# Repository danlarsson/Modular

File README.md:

# My Modular
My Modular Eurorack Synth

The plan is to build every module myself, with help from the all mighty internet to get schematics and tips.

KiCad 7.0 is used to create the schematics and PCBs.
PCBWay or JLCPCB is used for the PCBs.

# Planned Modules:

## 1. PSU: Power supply + Breakout board + Frontpanel
  - Power Supply 
    - [X] Design, [X] Order, [] Build, [] Test
 
  - Breakout board
    - [] Design, [] Order, [] Build, [] Test

  - Front panel
    - [] Design, [] Order, [] Build, [] Test

## 2. VCO: Voltage Conntrolled Oscillator
 ### VCO_1
  - [] Design, [] Order, [] Build, [] Test

## 3. VCF: Filter:

## 4. Envelope Generator:

## 5. LFO: Low Freq Oscillator

## 6. VCA: Voltage Controlled Amplifier

## 7. Mixer:

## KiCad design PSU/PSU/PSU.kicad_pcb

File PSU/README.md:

# PSU
A PowerSuply that converts 12-15V AC to +12, -12 and 5 Volts.
Containt 3 parts the PSU a Power Rail and a Front panel with a switch and LEDs.

# PDB
Power Distribution Board

# Front Panel
Front Panel for the PSU, with LED indicators and a Connector to get power for experiments.

## Idéas from:
https://www.patreon.com/moritzklein/posts?filters%5Btag%5D=PSU%20series

http://musicfromouterspace.com/analogsynth_new/WALLWARTSUPPLY/wallwart_added_load_rs_schem.pdf

## Parts:
6st - 4700uF 35V Elec Cap
https://www.lcsc.com/product-detail/Aluminum-Electrolytic-Capacitors-Leaded_CX-Dongguan-Chengxing-Elec-KM478M035L30RR0VH2FP0_C43354.html

6st 1uF 35V Tantalum Cap
https://www.lcsc.com/product-detail/span-style-background-color-ff0-Tantalum-span-Capacitors_Kyocera-AVX-TAP105K035SCS_C2987014.html

4st 1N4007  DO-41
https://www.lcsc.com/product-detail/Diodes-General-Purpose_ST-Semtech-1N4007_C106903.html

1st LC7812  TO-220
https://www.lcsc.com/product-detail/Linear-Voltage-Regulators-LDO_STMicroelectronics-L7812CV-DG_C2914.html

1st LC7912
https://www.lcsc.com/product-detail/Linear-Voltage-Regulators-LDO_STMicroelectronics-L7912CV_C111886.html

1st LC7805
https://www.lcsc.com/product-detail/Linear-Voltage-Regulators-LDO_STMicroelectronics-L7805CV_C111887.html

3st Heat Sink TO-220
https://www.lcsc.com/products/Heat-Sinks_441.html
https://www.lcsc.com/product-detail/Heat-Sinks_XSD-C4649_C4649.html

3st TO-220 Isolator
https://www.lcsc.com/product-detail/Heat-Sinks_Made-in-China-TO-220_C3010573.html

Skruv + Mutter + Isolator
https://www.lcsc.com/product-detail/Heat-Sinks_Made-in-China-C13380_C13380.html 

1st 16pin IDC Connector
https://www.lcsc.com/product-detail/span-style-background-color-ff0-IDC-span-span-style-background-color-ff0-Connectors-span_BOOMELE-Boom-Precision-Elec-C3406_C3406.html

1st 4pin screw terminal
https://www.lcsc.com/product-detail/span-style-background-color-ff0-Screw-span-span-style-background-color-ff0-terminal-span_DIBO-DB128L-5-0-4P-BU-S_C430599.html

1st 2pin screw terminal
https://www.lcsc.com/product-detail/Screw-terminal_DIBO-DB103-5-0-2P-BU-S_C430581.html

1st 2pin connector
?

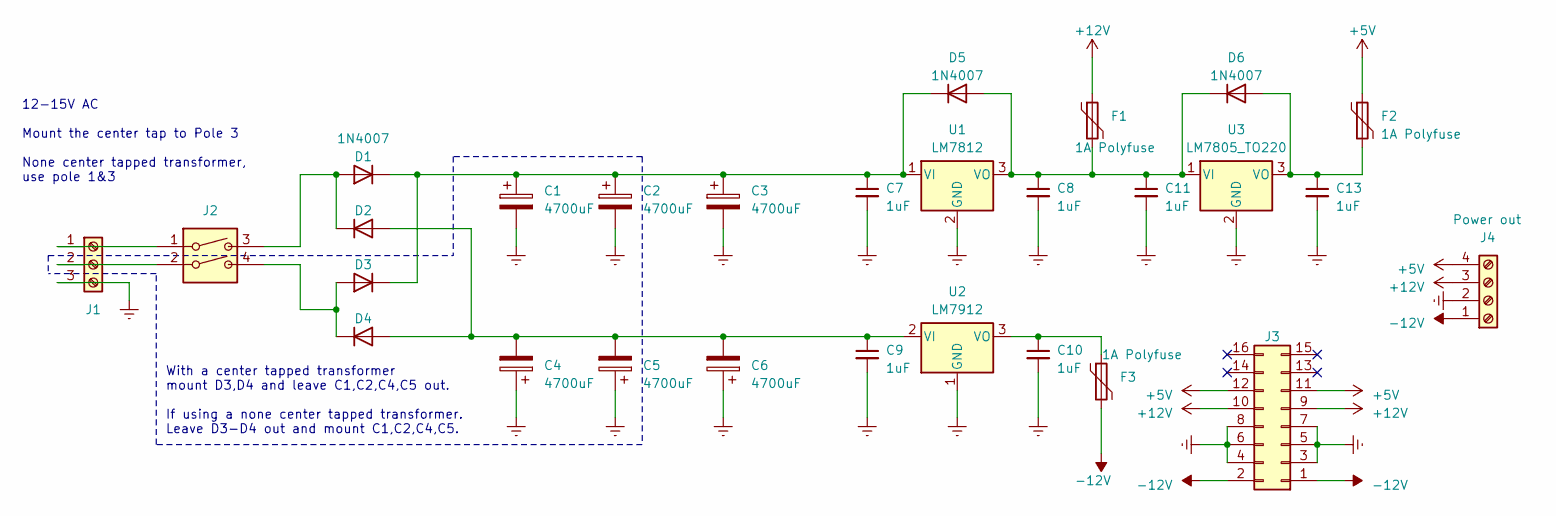
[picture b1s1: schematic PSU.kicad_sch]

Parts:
C1, C2, C3, C4, C5, C6: 4700uF; CP_Radial_D18.0mm_P7.50mm
C7, C8, C9, C10, C11, C13: 1uF; C_Rect_L7.0mm_W3.5mm_P5.00mm
D1, D2, D3, D4, D5, D6: 1N4007; D_DO-41_SOD81_P10.16mm_Horizontal
F1, F2, F3: 1A Polyfuse; Fuse_Bourns_MF-RHT200
J1: Screw_Terminal_01x03; JST_NV_B03P-NV_1x03_P5.00mm_Vertical
J2: SW_DIP_x02; PinSocket_2x02_P2.54mm_Vertical
J3: Conn_02x08_Odd_Even; IDC-Header_2x08_P2.54mm_Vertical
J4: Power out; JST_NV_B04P-NV_1x04_P5.00mm_Vertical
U1: LM7812; TO-220-3_Vertical
U2: LM7912; TO-220-3_Vertical
U3: LM7805_TO220; TO-220-3_Vertical

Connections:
+5V: F2.1, J3.11, J3.12, J4.4
+12V: F1.1, J3.9, J3.10, J4.3
-12V: F3.2, J3.1, J3.2, J4.1
GNDREF: C1.2, C2.2, C3.2, C4.1, C5.1, C6.1, C7.2, C8.2, C9.2, C10.2, C11.2, C13.2, J1.3, J3.3, J3.4, J3.5, J3.6, J3.7, J3.8, J4.2, U1.2 (GND), U2.1 (GND), U3.2 (GND)
unnamed: D1.2 (A), D2.1 (K), J2.3
unnamed: C1.1, C2.1, C3.1, C7.1, D1.1 (K), D3.1 (K), D5.1 (K), U1.1 (VI)
unnamed: C4.2, C5.2, C6.2, C9.1, D2.2 (A), D4.2 (A), U2.2 (VI)
unnamed: D3.2 (A), D4.1 (K), J2.4
unnamed: C8.1, C11.1, D5.2 (A), D6.1 (K), F1.2, U1.3 (VO), U3.1 (VI)
unnamed: C13.1, D6.2 (A), F2.2, U3.3 (VO)
unnamed: J1.1, J2.1
unnamed: J1.2, J2.2
unnamed: C10.1, F3.1, U2.3 (VO)

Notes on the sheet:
With a center tapped transformer mount D3,D4 and leave C1,C2,C4,C5 out. If using a none center tapped transformer. Leave D3-D4 out and mount C1,C2,C4,C5.
12-15V AC Mount the center tap to Pole 3 None center tapped transformer, use pole 1&3

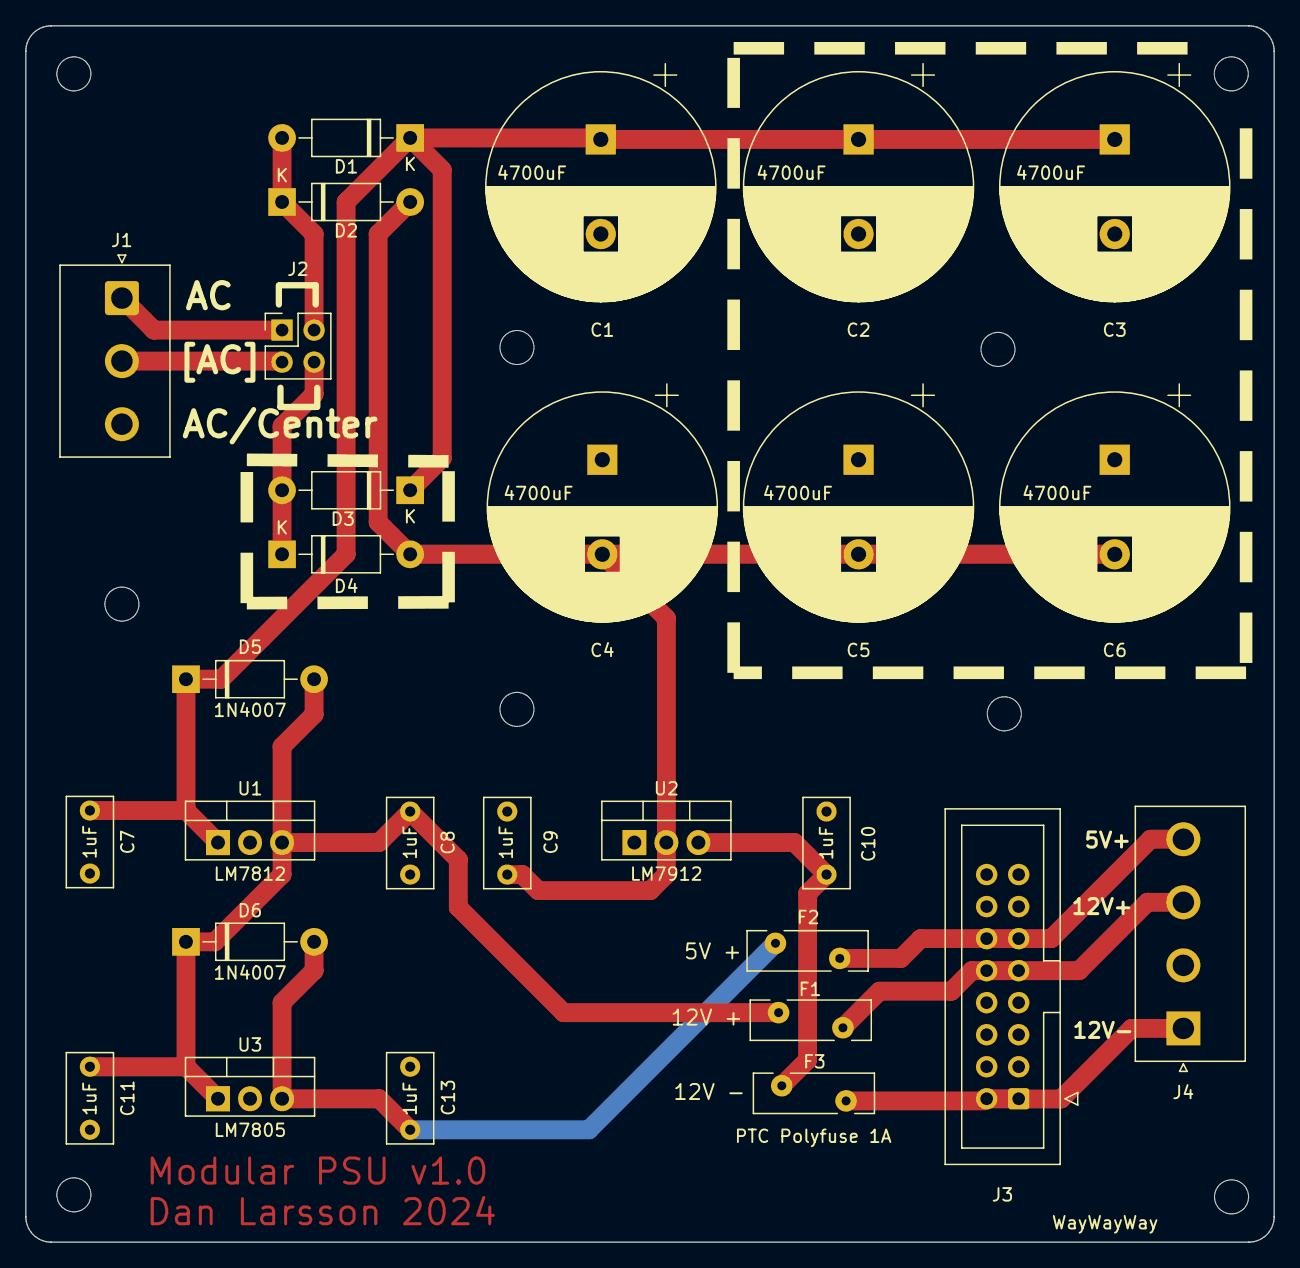
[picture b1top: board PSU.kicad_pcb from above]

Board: 2 copper layers, 99.0 x 96.5 mm, 28 parts (0 on the bottom side), 13 nets.

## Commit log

2023-04-26 ignore file
2023-04-26 ignore
2023-04-29 PSU work
2023-04-30 Remove .DS_Store
2023-04-30 Updates RM files
2024-11-23 Option for center tapped transformer
2024-11-23 PCD Fixed
2024-12-13 Pyssel
2024-12-13 Diverse
2024-12-13 Updated Readme files
2025-01-12 Started the VCO
2025-01-15 More work on the VCO
